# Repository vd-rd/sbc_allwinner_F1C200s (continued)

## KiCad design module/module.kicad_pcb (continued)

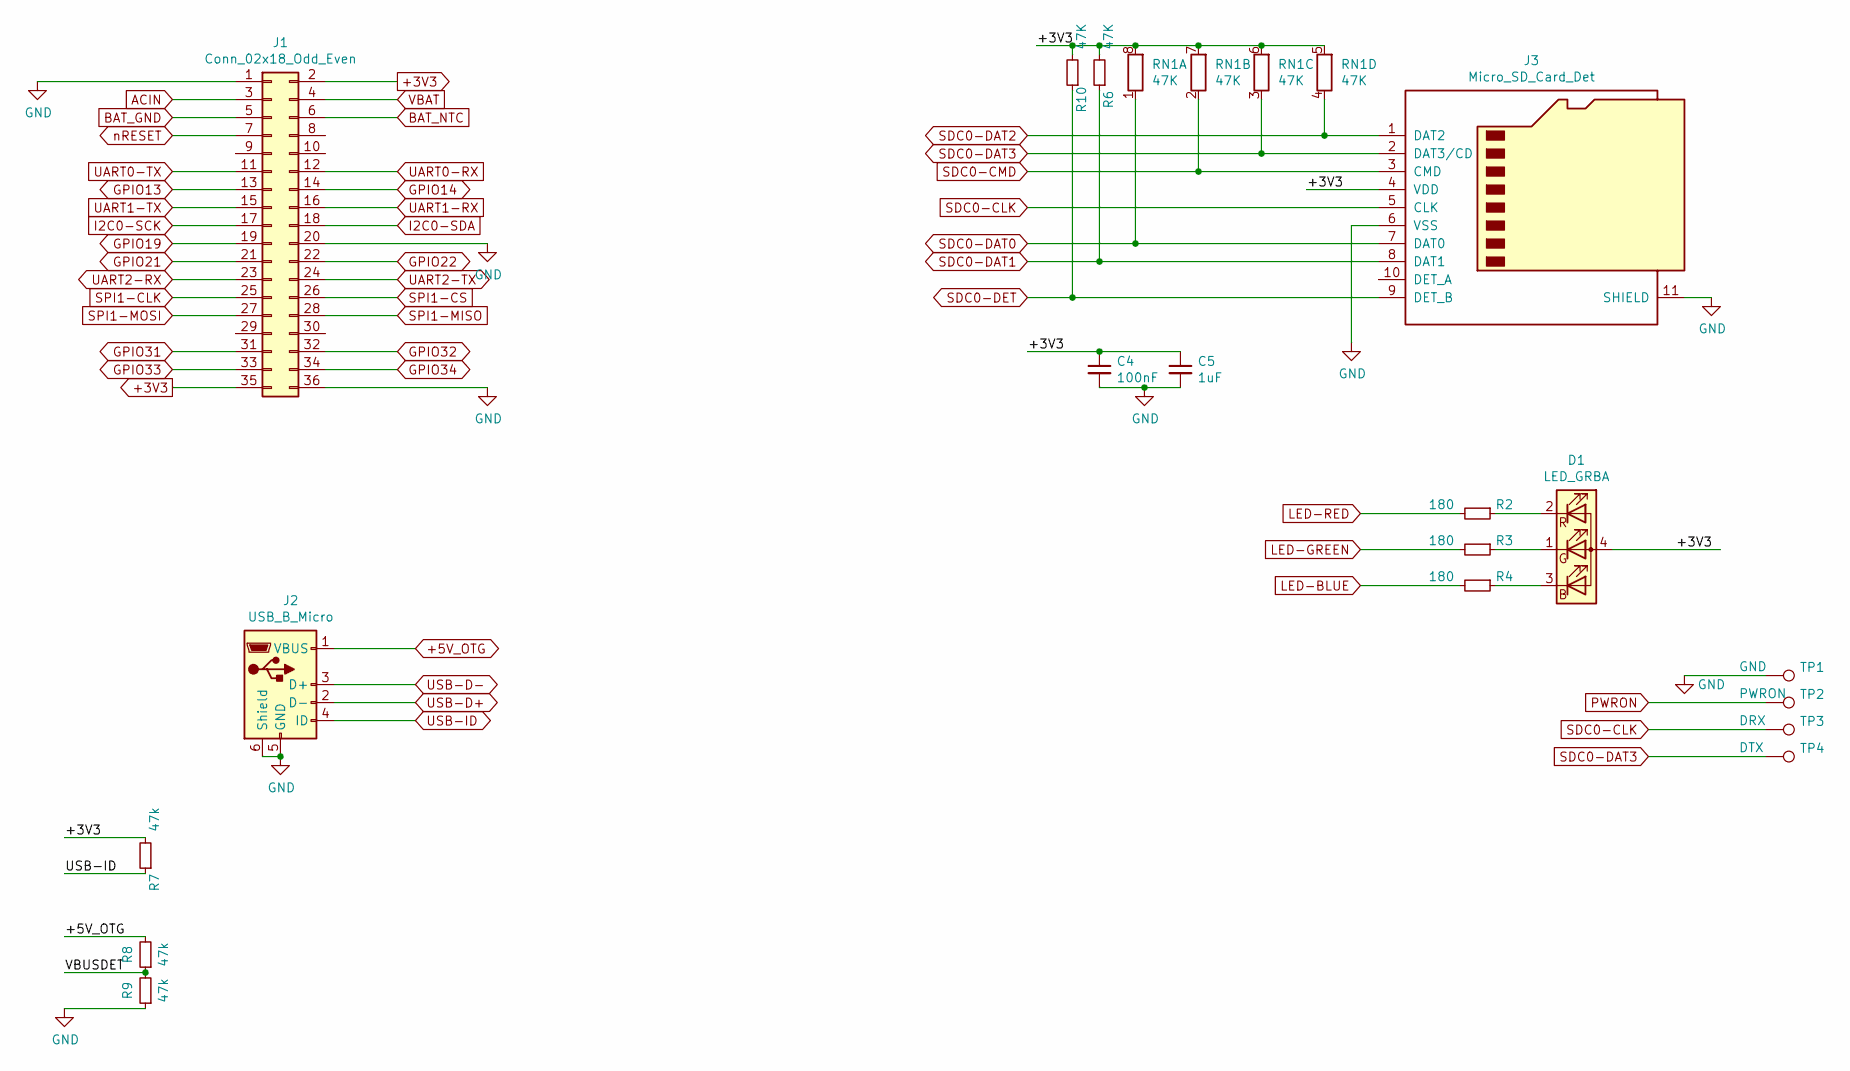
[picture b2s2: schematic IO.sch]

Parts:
C4: 100nF; C_0402_1005Metric
C5: 1uF; C_0402_1005Metric
D1: LED_GRBA; led-1204-rgba
J1: Conn_02x18_Odd_Even; PinHeader_2x18_P2.54mm_Vertical
J2: USB_B_Micro; USB_Micro-B_Amphenol_10103594-0001LF_Horizontal
J3: Micro_SD_Card_Det; 112J-TDAR-R01
R2, R3, R4: 180; R_0402_1005Metric
R6, R10: 47K; R_0402_1005Metric
R7, R8, R9: 47k; R_0402_1005Metric
RN1: 47K; R_Array_Convex_4x0402
TP1: GND; TestPoint_Pad_D1.0mm
TP2: PWRON; TestPoint_Pad_D1.0mm
TP3: DRX; TestPoint_Pad_D1.0mm
TP4: DTX; TestPoint_Pad_D1.0mm

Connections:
+3V3: C4.1, C5.1, D1.4 (A), J1.2, J1.35, J3.4 (VDD), R6.2, R7.2, R10.2, RN1.5 (R4.2), RN1.6 (R3.2), RN1.7 (R2.2), RN1.8 (R1.2); also elsewhere on the board
+5V_OTG: J2.1 (VBUS), R8.2; also elsewhere on the board
/IO/VBUSDET: R8.1, R9.2
ACIN: J1.3; also elsewhere on the board
BAT_GND: J1.5; also elsewhere on the board
BAT_NTC: J1.6; also elsewhere on the board
GND: C4.2, C5.2, J1.1, J1.20, J1.36, J2.5 (GND), J2.6 (Shield), J3.6 (VSS), J3.11 (SHIELD), R9.1, TP1.1; also elsewhere on the board
GPIO13: J1.13; also elsewhere on the board
GPIO14: J1.14; also elsewhere on the board
GPIO19: J1.19
GPIO21: J1.21; also elsewhere on the board
GPIO22: J1.22; also elsewhere on the board
GPIO31: J1.31; also elsewhere on the board
GPIO32: J1.32; also elsewhere on the board
GPIO33: J1.33; also elsewhere on the board
GPIO34: J1.34; also elsewhere on the board
I2C0-SCK: J1.17; also elsewhere on the board
I2C0-SDA: J1.18; also elsewhere on the board
LED-BLUE: R4.2; also elsewhere on the board
LED-GREEN: R3.2; also elsewhere on the board
LED-RED: R2.2; also elsewhere on the board
unnamed: D1.1 (GK), R3.1
unnamed: D1.2 (RK), R2.1
unnamed: D1.3 (BK), R4.1
PWRON: TP2.1; also elsewhere on the board
SDC0-CLK: J3.5 (CLK), TP3.1; also elsewhere on the board
SDC0-CMD: J3.3 (CMD), RN1.2 (R2.1); also elsewhere on the board
SDC0-DAT0: J3.7 (DAT0), RN1.1 (R1.1); also elsewhere on the board
SDC0-DAT1: J3.8 (DAT1), R6.1; also elsewhere on the board
SDC0-DAT2: J3.1 (DAT2), RN1.4 (R4.1); also elsewhere on the board
SDC0-DAT3: J3.2 (DAT3/CD), RN1.3 (R3.1), TP4.1; also elsewhere on the board
SPI1-CLK: J1.25; also elsewhere on the board
SPI1-CS: J1.26; also elsewhere on the board
SPI1-MISO: J1.28; also elsewhere on the board
SPI1-MOSI: J1.27; also elsewhere on the board
UART0-RX: J1.12; also elsewhere on the board
UART0-TX: J1.11; also elsewhere on the board
UART1-RX: J1.16; also elsewhere on the board
UART1-TX: J1.15; also elsewhere on the board
UART2-RX: J1.23; also elsewhere on the board
UART2-TX: J1.24; also elsewhere on the board
USB-ID: J2.4 (ID), R7.1
VBAT: J1.4; also elsewhere on the board
nRESET: J1.7; also elsewhere on the board

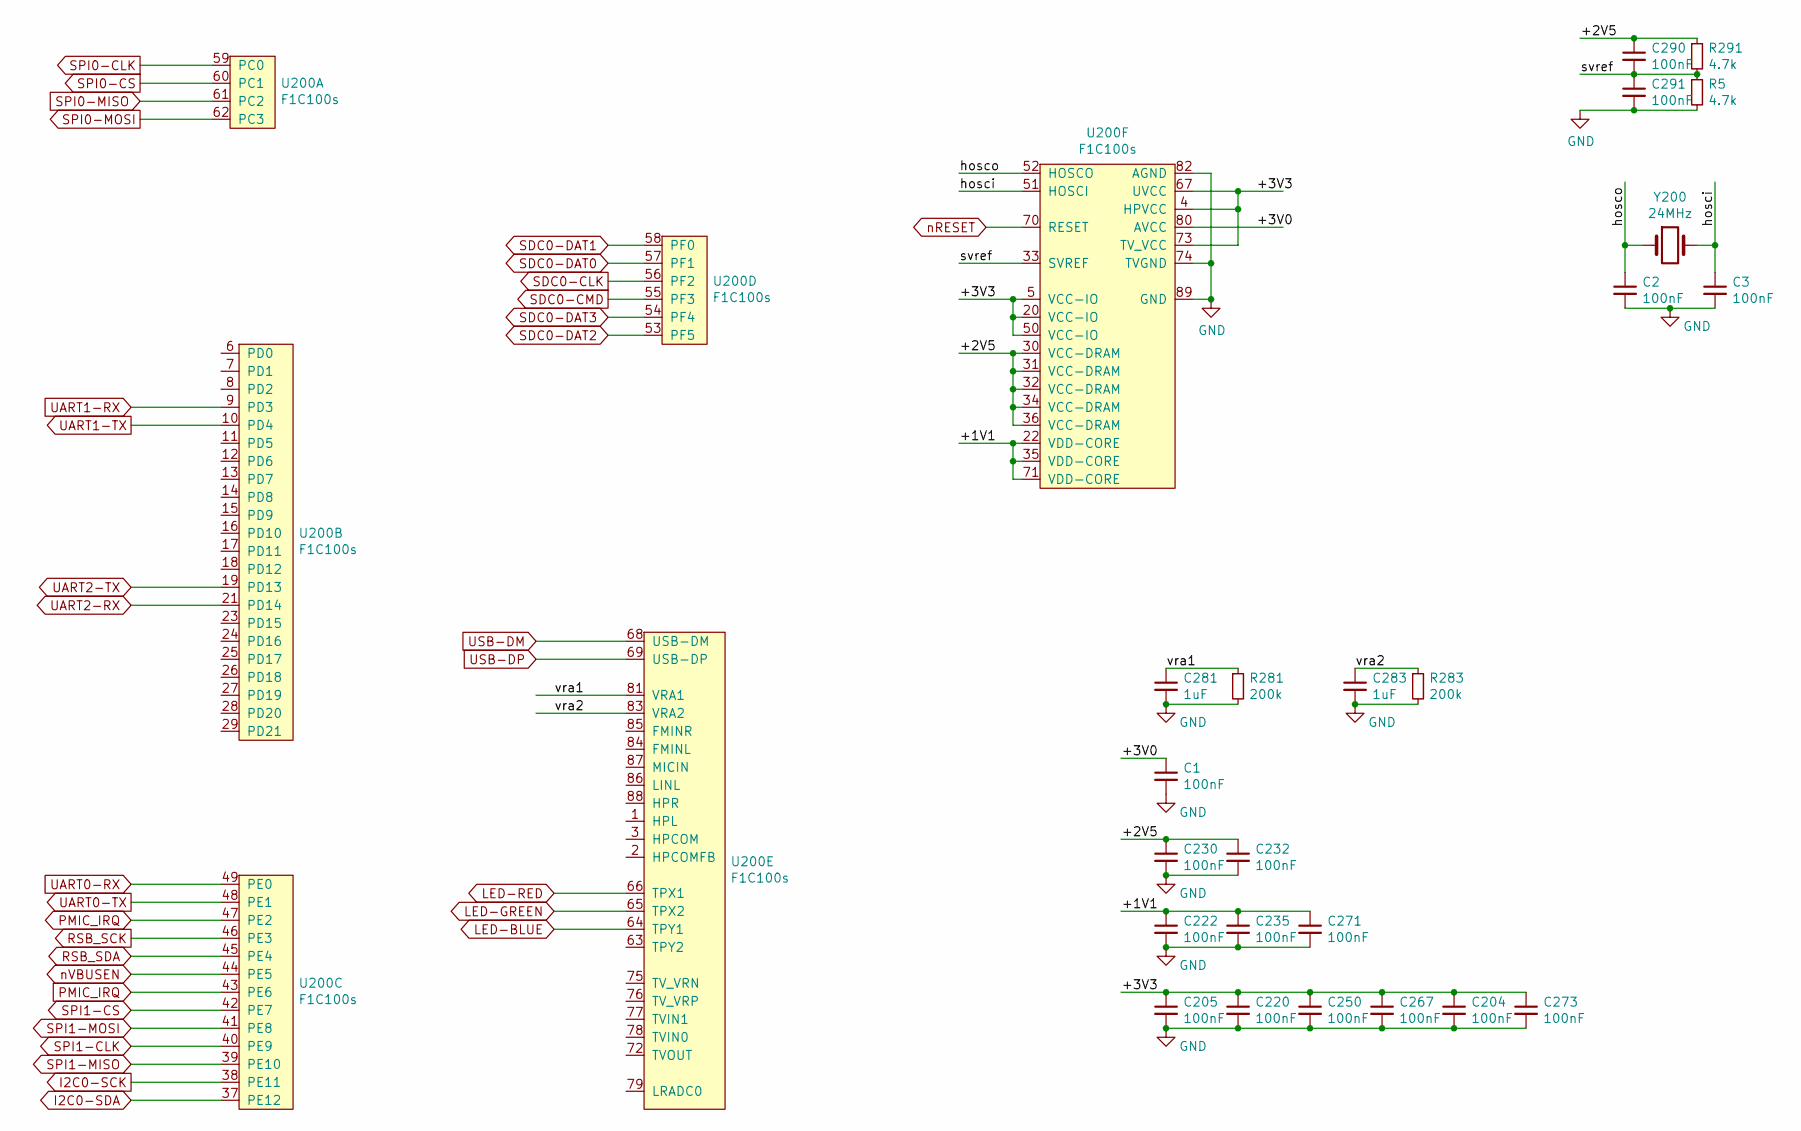
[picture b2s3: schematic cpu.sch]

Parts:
C1, C2, C3, C204, C205, C220, C222, C230, C232, C235, C250, C267, C271, C273, C290, C291: 100nF; C_0402_1005Metric
C281, C283: 1uF; C_0402_1005Metric
R5, R291: 4.7k; R_0402_1005Metric; Tolerance 1%
R281, R283: 200k; R_0402_1005Metric; Tolerance 1%
U200: F1C100s; QFN-88_EP_10x10_Pitch0.4mm
Y200: 24MHz; Crystal_SMD_3225-4Pin_3.2x2.5mm

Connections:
+1V1: C222.1, C235.1, C271.1, U200.22 (VDD-CORE), U200.35 (VDD-CORE), U200.71 (VDD-CORE); also elsewhere on the board
+2V5: C230.1, C232.1, C290.1, R291.1, U200.30 (VCC-DRAM), U200.31 (VCC-DRAM), U200.32 (VCC-DRAM), U200.34 (VCC-DRAM), U200.36 (VCC-DRAM); also elsewhere on the board
+3V3: C204.1, C205.1, C220.1, C250.1, C267.1, C273.1, U200.4 (HPVCC), U200.5 (VCC-IO), U200.20 (VCC-IO), U200.50 (VCC-IO), U200.67 (UVCC), U200.73 (TV_VCC); also elsewhere on the board
/CPU/+3V0: C1.1, U200.80 (AVCC)
/CPU/hosci: C3.1, U200.51 (HOSCI), Y200.2
/CPU/hosco: C2.1, U200.52 (HOSCO), Y200.1
/CPU/svref: C290.2, C291.1, R5.1, R291.2, U200.33 (SVREF)
/CPU/vra1: C281.1, R281.1, U200.81 (VRA1)
/CPU/vra2: C283.1, R283.1, U200.83 (VRA2)
GND: C1.2, C2.2, C3.2, C204.2, C205.2, C220.2, C222.2, C230.2, C232.2, C235.2, C250.2, C267.2, C271.2, C273.2, C281.2, C283.2, C291.2, R5.2, R281.2, R283.2, U200.74 (TVGND), U200.82 (AGND), U200.89 (GND); also elsewhere on the board
GPIO13: U200.15 (PD9); also elsewhere on the board
GPIO14: U200.14 (PD8); also elsewhere on the board
GPIO21: U200.13 (PD7); also elsewhere on the board
GPIO22: U200.12 (PD6); also elsewhere on the board
GPIO31: U200.11 (PD5); also elsewhere on the board
GPIO32: U200.8 (PD2); also elsewhere on the board
GPIO33: U200.7 (PD1); also elsewhere on the board
GPIO34: U200.6 (PD0); also elsewhere on the board
I2C0-SCK: U200.38 (PE11); also elsewhere on the board
I2C0-SDA: U200.37 (PE12); also elsewhere on the board
LED-BLUE: U200.64 (TPY1); also elsewhere on the board
LED-GREEN: U200.65 (TPX2); also elsewhere on the board
LED-RED: U200.66 (TPX1); also elsewhere on the board
RSB_SCK: U200.46 (PE3); also elsewhere on the board
RSB_SDA: U200.45 (PE4); also elsewhere on the board
SDC0-CLK: U200.56 (PF2); also elsewhere on the board
SDC0-CMD: U200.55 (PF3); also elsewhere on the board
SDC0-DAT0: U200.57 (PF1); also elsewhere on the board
SDC0-DAT1: U200.58 (PF0); also elsewhere on the board
SDC0-DAT2: U200.53 (PF5); also elsewhere on the board
SDC0-DAT3: U200.54 (PF4); also elsewhere on the board
SPI0-CLK: U200.59 (PC0); also elsewhere on the board
SPI0-CS: U200.60 (PC1); also elsewhere on the board
SPI0-MISO: U200.61 (PC2); also elsewhere on the board
SPI0-MOSI: U200.62 (PC3); also elsewhere on the board
SPI1-CLK: U200.40 (PE9); also elsewhere on the board
SPI1-CS: U200.42 (PE7); also elsewhere on the board
SPI1-MISO: U200.39 (PE10); also elsewhere on the board
SPI1-MOSI: U200.41 (PE8); also elsewhere on the board
UART0-RX: U200.49 (PE0); also elsewhere on the board
UART0-TX: U200.48 (PE1); also elsewhere on the board
UART1-RX: U200.9 (PD3); also elsewhere on the board
UART1-TX: U200.10 (PD4); also elsewhere on the board
UART2-RX: U200.21 (PD14); also elsewhere on the board
UART2-TX: U200.19 (PD13); also elsewhere on the board
VBUSDET: U200.63 (TPY2)
nRESET: U200.70 (RESET); also elsewhere on the board
nVBUSEN: U200.44 (PE5); also elsewhere on the board

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
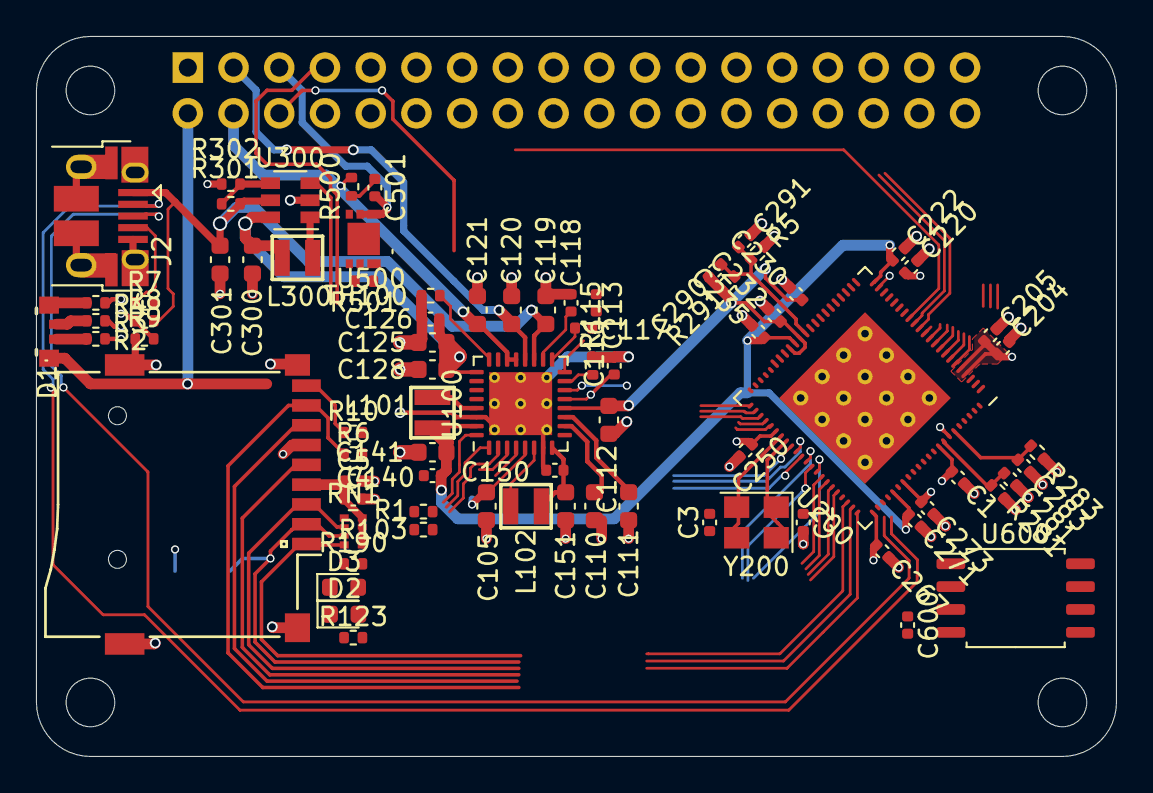
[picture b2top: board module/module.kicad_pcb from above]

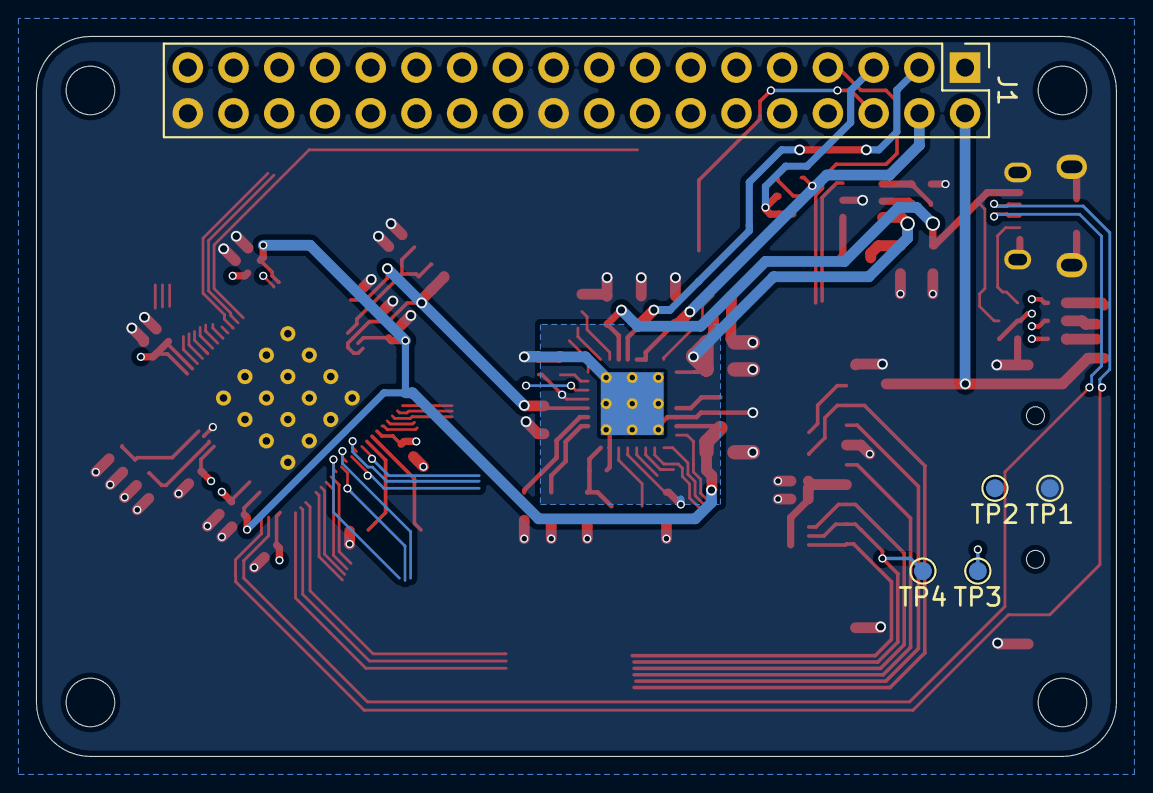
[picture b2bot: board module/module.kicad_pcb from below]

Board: 2 copper layers, 60.0 x 40.0 mm, 84 parts (5 on the bottom side), 77 nets.

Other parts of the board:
C600: 100nF; C_0402_1005Metric
U600: W25Q32JVSS; SOIC-8_5.23x5.23mm_P1.27mm

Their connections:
+3V3: C600.1, U600.8; also elsewhere on the board
GND: C600.2, U600.4; also elsewhere on the board
SPI0-CLK: U600.6; also elsewhere on the board
SPI0-CS: U600.1; also elsewhere on the board
SPI0-MISO: U600.2; also elsewhere on the board
SPI0-MOSI: U600.5; also elsewhere on the board

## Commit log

2021-03-06 first kicad project
2021-03-07 add pmic schematic
2021-03-07 add io and cpu
2021-03-07 add io connectors
2021-03-07 board improvements
2021-03-08 define connections
2021-03-10 define component placing
2021-03-10 define IO connections
2021-03-10 Backlink to CADLAB.io has been added.
2021-03-11 redefine connections
2021-06-13 updated project
2021-09-02 updated gitignore
2021-09-02 project restructure
2021-10-04 project cleanup
2021-10-04 improve floorplan and change pmic to axp173
2021-10-04 add 3v3 rail
2021-10-04 revert to two layer design
2021-10-06 updates on features and layout
2021-10-09 add header pins
2021-10-10 routing for signals
2021-10-10 power stage routed
2021-10-16 more routing
2021-10-24 defined cpu signals
2021-10-25 added 3d models
2021-10-26 more cosmetic fixes
2022-01-16 add layer identification labels
2022-03-24 small udpates
2022-04-16 add audio block
2022-04-20 redesign board connections
2022-05-07 add port expander
2024-03-31 bump to kicad 8
2024-07-02 added wireless networking
2024-07-03 finished sdio bus for sd card
2024-07-04 add wip render
2024-07-04 added silkscreen info
